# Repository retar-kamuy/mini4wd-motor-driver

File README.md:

# Mini 4WD Motor Driver 開発版

[keimyojizai/mini4wd-motor-driver](https://github.com/keimyojizai/mini4wd-motor-driver) を元に開発している [retar-kamuy のフォーク](https://github.com/retar-kamuy/mini4wd-motor-driver) です。

**基板は設計検証中です。製造・発注には使用できません。** Q2修正後のDRC/ERCは0件ですが、電流経路、部品・ランド、機構、EMCと製造データの確認が残っています。

| 内容 | 正本・入口 |
|---|---|
| 現行KiCad設計 | [hardware/kicad/mini4wd-motor-driver](hardware/kicad/mini4wd-motor-driver/) |
| 基板の残課題 | [specs/003-resolve-pcb-drc/tasks.md](specs/003-resolve-pcb-drc/tasks.md) |
| ファームウェア | [firmware/mini4ai_v358](firmware/mini4ai_v358/) |
| Webアプリ | [web/index.html](web/index.html) |
| 利用資料 | [docs](docs/) |
| 開発環境 | [SETUP.md](SETUP.md) |
| 構成と来歴 | [docs/repository_structure.md](docs/repository_structure.md) |

以下は元プロジェクトを基にした利用案内です。掲載された既存基板の写真・動作説明は、開発中のKiCad基板の製造承認を意味しません。

---

# ミニ四駆AI モータードライバ基板

**XIAO MG24 Sense専用 / 正転専用 / ショートブレーキ対応 MOSFETドライバ**

ミニ四駆に電子制御を追加するための、  
**XIAO MG24 Sense専用 高電流モータードライバ基板**です。

- **Nch MOSFETによるモーター駆動**
- **Pch MOSFETによるショートブレーキ**
- **1本のPWM信号で駆動 / 制動を切り替え**
- **発進時のソフトスタートに対応**
- **電池電圧・M-側電圧・基板温度の観測に対応**
- **Ni-MH 2セル / Li-ion 1セル向け**

> 本基板は、改造・競技・研究・教育用途を想定した電子工作向け部品です。  
> はんだ付け、配線、電源極性、モーター制御に関する基礎知識が必要です。

---

## 購入後に使用するもの

本基板を使用するには、XIAO MG24 Senseへ専用ファームウェアを書き込み、WebアプリからBLE接続して設定・走行制御を行います。

- [Webアプリを開く](https://keimyojizai.github.io/mini4wd-motor-driver/)
- [Windows書き込みツールをダウンロード](https://github.com/keimyojizai/mini4wd-motor-driver/releases/latest)
- [ファームウェア更新手順](docs/firmware_update.md)
- [本体へ保存とスタンドアローン起動](docs/standalone_mode.md)
- [Arduino IDEで手動書き込みする手順](docs/flash_arduino_ide.md)
- [書き込みに失敗した場合の復旧手順](docs/recovery.md)

### Webアプリでできること

- デバイスへのBLE接続
- 走行開始・停止
- 認識調整
- ルール設定
- かんたん設定で、90度/180度/それ以上のカーブ継続を別々に選択
- 別画面のかんたん設定ウィザード（1画面1判断）
- かんたん設定内で2つ目・3つ目のルールを追加可能
- かんたん設定中は専用ルールセットだけを走行に反映し、過去ルールとの重複発火を防止
- 目的位置の手前を起点にした時間差アクション設定
- 電圧補正設定
- ラップタイム確認
- 停止後ログ確認
- ヘッダー非表示による走行・ラップ表示の拡大
- ファームウェアバージョン確認
- BLE表示名の変更
- 現在の設定を本体へ保存
- 保存済み設定によるスタンドアローン起動

### 初回ファームウェア書き込み

初回使用時、またはファームウェア更新時は、Windows用書き込みツールを使用してください。

1. GitHub ReleasesからWindows用書き込みツールをダウンロードします。
2. ZIPを右クリックして「すべて展開」します。
3. 展開したフォルダ内の `START_HERE_Flash_Mini4AI.cmd` を実行します。
4. 書き込み時に、BLE表示名を自由に設定できます。

> ファームウェア書き込み時は、**ミニ四駆側の電源をオフ** にしてからUSB接続してください。

macOS / Linux用の書き込みツールは、現時点では動作確認対象外のため同梱していません。Windows用書き込みツールでうまくいかない場合や、他OSで使用する場合はArduino IDEで手動書き込みしてください。

### 本体へ保存とスタンドアローン起動

Webアプリで設定した内容には、**一時適用**と**本体へ保存**があります。

- **走行開始**: 現在の画面設定を一時的に本体へ送信して走行します。電源を切ると、この一時設定は残りません。
- **本体へ保存**: 現在のパラメータ、ルール、電圧補正、周回認識設定をXIAO MG24 Sense本体へ保存します。
- **スタンドアローン起動**: 保存済み設定がある状態で、裏返しのまま電源ON → 表向きに戻す → 約3秒後にBLEなしで自動スタートします。

スタンドアローン起動で使いたい設定は、必ずWebアプリ左メニューの **「本体へ保存」** を押してから使用してください。

Webアプリでは、誤操作を避けるため「走行開始」「停止」とは離した左メニューに **本体へ保存** を配置しています。保存時には確認画面で「はい / いいえ」を選択します。

詳細は [本体へ保存とスタンドアローン起動](docs/standalone_mode.md) を参照してください。

### かんたん設定モード

Webアプリには、通常の詳細UIとは別に、1画面1判断で進む **かんたん設定** があります。
目的位置、起点セクション、発動回数、待機時間、ブレーキ/低出力を順番に設定できます。

走行後に「早すぎた」「遅すぎた」「発動しなかった」「違う場所でも発動した」を選ぶと、修正すべき画面へ戻ります。
このとき、改善アドバイスを画面上部に表示し続けるため、何を直すべきか確認しながら調整できます。

1つ目のルールが決まった後も、かんたん設定のまま2つ目・3つ目のルールを追加できます。

### 推奨バージョン

| 項目 | 推奨バージョン |
|---|---|
| Webアプリ | v4.21-r33 |

かんたん設定では単発の左C/右Cを初期状態で非表示にし、誤発動しにくい左/右カーブ継続を基本にしています。
| ファームウェア | v3.58-r10 |

Webアプリ上で、接続中デバイスのファームウェアバージョンを確認できます。

---

## 外観・パッケージ・装着例

### 基板単体

### 販売パッケージ

### ミニ四駆への装着例

> 装着例です。ミニ四駆車体、XIAO MG24 Sense、モーター、電池、配線材等は付属しません。

### 動作例

[YouTube Shortsで動作例を見る](https://youtube.com/shorts/a6D7kiM3N_Y?feature=share)

---

## どのような基板か

本基板は、ミニ四駆で一般的な

```text
M+ / B+ = 電池＋ / モーター＋ 共通
M-      = モーター−
B-      = 電池−
```

という構成を前提にした、**正転専用・M-側制御**のモータードライバです。

Hブリッジではなく、機能を

- **正転駆動**
- **ショートブレーキ**
- **各種センシング**

に絞ることで、ミニ四駆AI制御向けに小型化と高電流駆動を狙っています。

---

## 主な特徴

- **XIAO MG24 Sense専用設計**
- **正転専用**。逆転制御には非対応
- **Nch MOSFETによる低側駆動**
- **Pch MOSFETによるショートブレーキ**
- **UCC27511による5Vゲート駆動**
- **TPS61023による5V昇圧電源**
- **XIAO MG24 Senseへの5V給電**
- **VBAT / MID / 温度の観測に対応**
- **発進時のソフトスタートに対応**
- **DRV8835系ドライバでは駆動できなかったモーターの駆動を手元評価で確認**

---

## ソフトウェア制御について

本基板は、XIAO MG24 Sense上のファームウェアでモーターを制御します。

- 走行開始時は、設定されたDutyへ一気に上げず、短時間のソフトスタートを行います。
- 走行中のルール判定、ブレーキ、低出力制御は本体側で実行されます。
- Webアプリは、設定・開始/停止指示・ログ確認を行うための操作画面です。
- Webアプリの走行開始は、現在の画面設定を一時適用します。
- スタンドアローン起動で使う設定は、Webアプリの **「本体へ保存」** を押したときだけ更新されます。
- BLE接続が切れても、走行中の制御判断は本体側で継続します。

## ルール設計の基本

目的の場所で止める、または減速する場合は、**その場所そのものを認識してからブレーキするのではなく、手前の特徴的なセクションを起点にして時間差でアクション**します。

例として、ウェーブで止まりたい場合、ウェーブを認識してからブレーキすると遅れることがあります。ウェーブの手前にある特徴的なセクションを起点にし、待機msで位置を合わせてからブレーキ/低出力を出します。

最初は1〜2セグメントの短い条件で作り、同じ起点が複数回出る場合は、奇数回・偶数回・N回のみの発動条件を使います。

Webアプリの **かんたん設定** は通常画面とは別画面で開き、1画面につき1つの判断だけを表示します。
最後の接続前には、設定したルールを自然文で確認できます。
走行後は「発動しない」「早すぎる」「遅すぎる」「余計な場所でも出る」から選ぶと、次に触るべき設定を1つに絞って提案します。

詳細は [かんたん設定ウィザード](docs/guided_setup.md) を参照してください。

---

## 重要な注意事項

使用前に必ず確認してください。

```text
・XIAO MG24 Sense専用です
・XIAO MG24 Senseは付属しません
・正転専用です
・逆転制御はできません
・Hブリッジではありません
・PWM Duty 0%ではショートブレーキになります
・電池の逆接続は禁止です
・Li-ion 2セルは禁止です
・8.4V系電源は禁止です
・FM-A / SFMシャーシには基本的に非対応です
・フェンスカー等の電池逆向き運用には、そのまま使用できません
・ファームウェア書き込み時は、ミニ四駆側の電源をオフにしてからUSB接続してください
```

---

## 基本仕様

| 項目 | 内容 |
|---|---|
| 対応マイコン | XIAO MG24 Sense専用 |
| 駆動方式 | 正転専用、M-側制御 |
| モーター制御 | Nch MOSFET低側駆動 |
| ブレーキ | Pch MOSFETによるショートブレーキ |
| 制御信号 | PWM入力 1本 |
| 想定電源 | Ni-MH 2セル / Li-ion 1セル |
| 非対応電源 | Li-ion 2セル、8.4V系電源 |
| 基板サイズ | 約 55 mm × 21 mm |
| 基板厚 | 1.2 mm |

---

## 接続概要

### 大電流端子

```text
M+ / B+ = 電池＋ / モーター＋ 共通
M-      = モーター−
B-      = 電池−
```

### XIAO MG24 Senseとのピン対応

| XIAO MG24 Sense | 本基板での機能 |
|---|---|
| 5V | 5V OUT |
| GND | GND |
| PC0（D0） | VBAT SENSE |
| PC1（D1） | NTC TEMP |
| PC2（D2） | MOTOR PWM |
| PC3（D3） | MID SENSE |

---

## 詳細ドキュメント

READMEでは概要のみを示しています。  
設計意図・配線・動作原理・注意事項の詳細は、以下を参照してください。

- [ファームウェア更新手順](docs/firmware_update.md)
- [本体へ保存とスタンドアローン起動](docs/standalone_mode.md)
- [Arduino IDEで手動書き込みする手順](docs/flash_arduino_ide.md)
- [書き込みに失敗した場合の復旧手順](docs/recovery.md)
- [トラブルシュート](docs/troubleshooting.md)
- [かんたん設定ウィザード](docs/guided_setup.md)
- [ハードウェア仕様と主要部品](docs/hardware_spec.md)
- [配線・取り付け・対応シャーシ](docs/wiring_and_usage.md)
- [PWM制御とショートブレーキの動作](docs/pwm_and_brake.md)
- [安全上の注意・免責事項・サポート](docs/safety_and_support.md)

---

## サポート

不具合報告・質問・改善提案は、GitHubの **Issues** を使用してください。  
問い合わせ時は、以下の情報を記載してください。

- 使用しているWebアプリのバージョン
- 使用しているファームウェアのバージョン
- XIAO MG24 SenseのBLE表示名
- 使用電源
- 使用モーター
- 症状が起きた操作手順
- 可能であれば、Webアプリの停止後ログ

---

## 商標について

- ミニ四駆は株式会社タミヤの登録商標です。
- 本基板は株式会社タミヤの公式製品・公認製品ではありません。
- 本基板は個人開発の改造・実験用基板です。

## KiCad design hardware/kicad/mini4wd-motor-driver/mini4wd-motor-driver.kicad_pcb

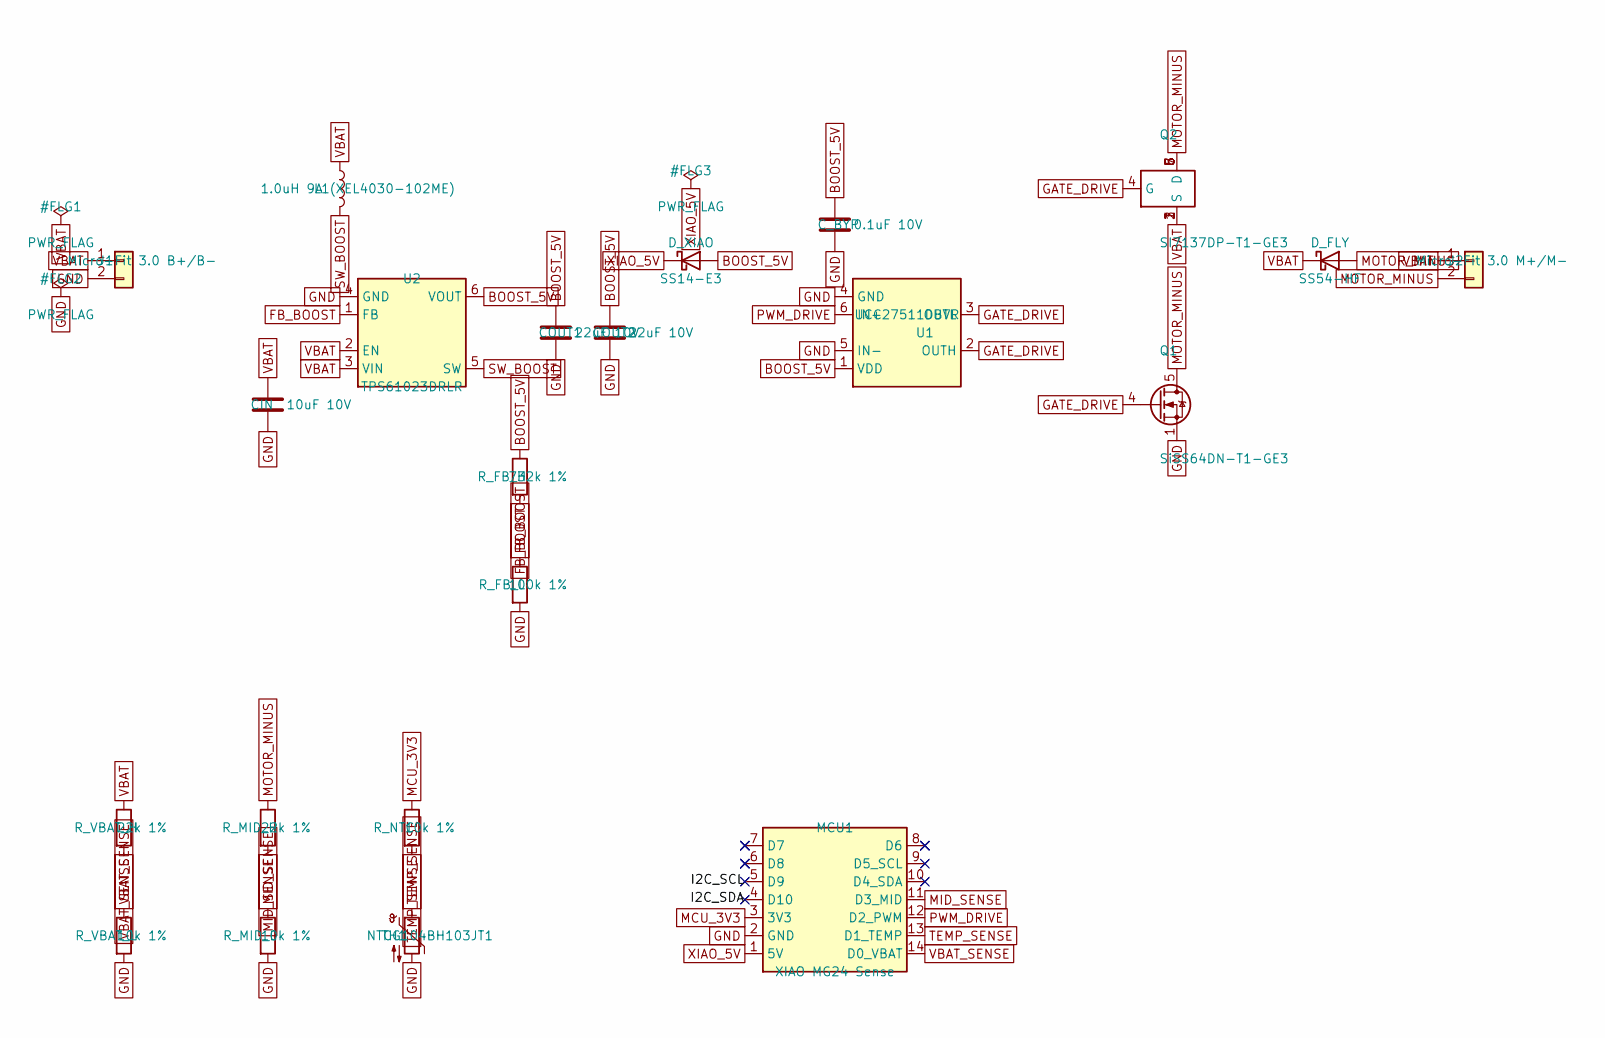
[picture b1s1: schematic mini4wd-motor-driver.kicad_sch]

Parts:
CIN: 10uF 10V; C_0603_1608Metric
COUT1, COUT2: 22uF 10V; C_0603_1608Metric
C_BYP: 0.1uF 10V; C_0402_1005Metric
D_FLY: SS54-HF; D_SMA
D_XIAO: SS14-E3; D_SMA
J1: Micro-Fit 3.0 B+/B-; Molex_MicroFit30_43650-0214
J2: Micro-Fit 3.0 M+/M-; Molex_MicroFit30_43650-0214
L1: 1.0uH 9A (XEL4030-102ME); Coilcraft_XEL4030
MCU1: XIAO MG24 Sense; XIAO_MG24_Castellated_14P
Q1: SiSS64DN-T1-GE3; Vishay_PowerPAK_1212-8_Single
Q2: SI7137DP-T1-GE3; PowerPAK_SO-8_SI7137DP
R_FB_H: 732k 1%; R_0603_1608Metric
R_FB_L: 100k 1%; R_0603_1608Metric
R_MID_H: 22k 1%; R_0603_1608Metric
R_MID_L: 10k 1%; R_0603_1608Metric
R_NTC: 10k 1%; R_0603_1608Metric
R_VBAT_H: 22k 1%; R_0603_1608Metric
R_VBAT_L: 10k 1%; R_0603_1608Metric
TH1: NTCG104BH103JT1; R_0402_1005Metric
U1: UCC27511DBVR; SOT-23-6
U2: TPS61023DRLR; Texas_R-PDSO-N6_DRL-6

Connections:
/I2C_SCL: MCU1.5 (D9)
/I2C_SDA: MCU1.4 (D10)
BOOST_5V: COUT1.1, COUT2.1, C_BYP.1, D_XIAO.2 (A), R_FB_H.1, U1.1 (VDD), U2.6 (VOUT)
FB_BOOST: R_FB_H.2, R_FB_L.1, U2.1 (FB)
GATE_DRIVE: Q1.4 (G), Q2.4 (G), U1.2 (OUTH), U1.3 (OUTL)
GND: CIN.2, COUT1.2, COUT2.2, C_BYP.2, J1.2, MCU1.2 (GND), Q1.1 (S), Q1.2 (S), Q1.3 (S), R_FB_L.2, R_MID_L.2, R_VBAT_L.2, TH1.2, U1.4 (GND), U1.5 (IN-), U2.4 (GND)
MCU_3V3: MCU1.3 (3V3), R_NTC.1
MID_SENSE: MCU1.11 (D3_MID), R_MID_H.2, R_MID_L.1
MOTOR_MINUS: D_FLY.2 (A), J2.2, Q1.5 (D), Q2.5 (D), Q2.6 (D), Q2.7 (D), Q2.8 (D), R_MID_H.1
PWM_DRIVE: MCU1.12 (D2_PWM), U1.6 (IN+)
SW_BOOST: L1.2, U2.5 (SW)
TEMP_SENSE: MCU1.13 (D1_TEMP), R_NTC.2, TH1.1
VBAT: CIN.1, D_FLY.1 (K), J1.1, J2.1, L1.1, Q2.1 (S), Q2.2 (S), Q2.3 (S), R_VBAT_H.1, U2.2 (EN), U2.3 (VIN)
VBAT_SENSE: MCU1.14 (D0_VBAT), R_VBAT_H.2, R_VBAT_L.1
XIAO_5V: D_XIAO.1 (K), MCU1.1 (5V)

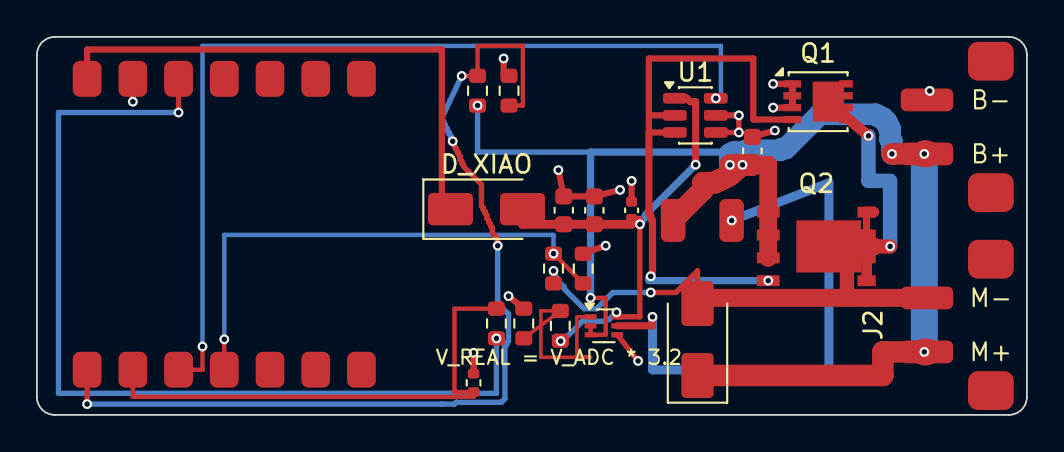
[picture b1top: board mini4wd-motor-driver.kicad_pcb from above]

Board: 2 copper layers, 55.0 x 21.0 mm, 22 parts (0 on the bottom side), 13 nets.
